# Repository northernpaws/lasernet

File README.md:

# Lasernet

This repository contains the software, hardware, and CAD files for retrofitting lasertag.net Falcon systems with an open-source platform. This involves replacing the PCBs in the tagger and vest units with new Zigbee-controlled PCBs, and having a computer with a Zigbee radio to communicate with them and run the game supervisor software. Additional devices, such as tablets, can be used to manage games over a web interface.

This project is currently a work-in-progress until release v1.0.0. More details for how to assemble the system will be added below as it evolves.

[Tagger Schematics (KiCanvas)](https://kicanvas.org/?github=https%3A%2F%2Fgithub.com%2Fnorthernpaws%2Flasernet%2Fblob%2Fmain%2Ftagger%2Fhardware%2Ftagger.kicad_pro)

## Components

 - An existing lasertag.net Falcon system
 - The retrofit PCBs for the taggers and vests
 - A computer to run the game supervisor
 - A Zigbee interface for the supervisor computer

### Game Supervisor/Controller Computer

For this system you need some type of computer to run the Zigbee interface and game controller software that connects to the units and manages their state, health, etc.

This PC replaces the need for all the units in the system to connect back to an Android tablet over Wifi like the stock laserag.net system does, eliminating Wifi instability from the tablet sleeping, being powered off, battery running out, etc.

We particularly like refurbished Lenovo ThinkCentre Tiny's (such as the M900) for their compact size, power management features (such as auto-power on after power loss), multi-display options, ample USB powers, and an ethernet port, Wifi, and Bluetooth package that gives many options for connectivity. Their reburbished prices are also incredibly afforable, with an M900 with an i7 coming in at around $100CAD, and being office PCs their refurbishment condition tends to be excellent.

### Computer to Zigbee Interface

To communicate with the new units you'll need some type of Zigbee radio or relay that can serve as the Zigbee network coordinator, and allow the PC running the management software to communicate with it. 

Initial software support will be for XBee 3 units in API Mode connected over USB serial, and Texas Instruments Z-Stack devices such as the SMLIGHT SLZB-06M.

We personally like the SMLIGHT SLZB-06M as it can be powered with PoE, simplifying running it to a mount ~12ft up the wall by using a single cable without needing to source additional power at the mounting location. The SLZB-06M is also highly configurable, has suitable range for most indoor arenas, all bundled up into a nice small and portable package that's easy to mount.

## Motivation

I was hired early in 2025 by a center to help repair their lasertag.net Falcon system. The more units I repaired, the more I discovered just how poorly designed the electronics and software components where. The failing units are becoming so regular that I cannot reasonably keep up with them, I'm up to fixing about 5-7 a week with common failures that could have be completely avoided with better mechanical and software design and robust testing that lasertag.net should have done.

I was in regular contact with technical support from the company for several weeks, until they stopped responding after I asked them to connect me to someone I could arrange warrenty repairs with. Likewise, the owner of the business was speaking to their sale representative and a marketing director, who both stopped responding when he asked about repairs and replacement parts. 

The electronics are missing essential safety components, such as a battery charge controller, and some use bad batches of the outdated ESP-12-E (ESP8266 MOD) modules that I've had to replace with the newer ESP-12-F modules on several units to solve Wifi connection problems. The mechanical design around the electronics is also full of issues, such as lacking strain relief on some cables ripping JST connectors off the circuit board under certain common failure conditions.

The software is not robust - missing retry and reconnection mechanisms that cause any minor Wifi instability to result in units dropping out of ongoing games, with no mechanism to reconnect them when they're connected again moments later. The software also relies on all of the game units (possible 20-40+ devices depending on the setup!) having a stable connection to a TCP server running on an Android tablet. If the tablet sleeps, then packets start to be dropped or delayed and causes a myriad of game glitches.

These ongoing issues, and more, have caused the center to loose very large party bookings due to a lack of functional units limiting laser tag game sizes, and have left many players frustrated when a unit fails mid-game and they can't participate.

## Roadmap

Since the business has all of these tagger and vest units that have rebust shells and sewing, we've decided as a "Phase 1" to replace all of the PCBs in the taggers and vests with our own, and then connect them to our own set of software for game management. This will give the business full control over how the system runs, where the failure points are, and allow us to set up a system that's easier for the staff to run and manage.

I'm providing the sources here for anyone else who may be having issues. The goal is that we reach a v2 of this repository where we have the PCB sources files, firmware, and software components required all bundled together into an easily usable package. Eventually I may look at selling replacement retrofit kits and guides.

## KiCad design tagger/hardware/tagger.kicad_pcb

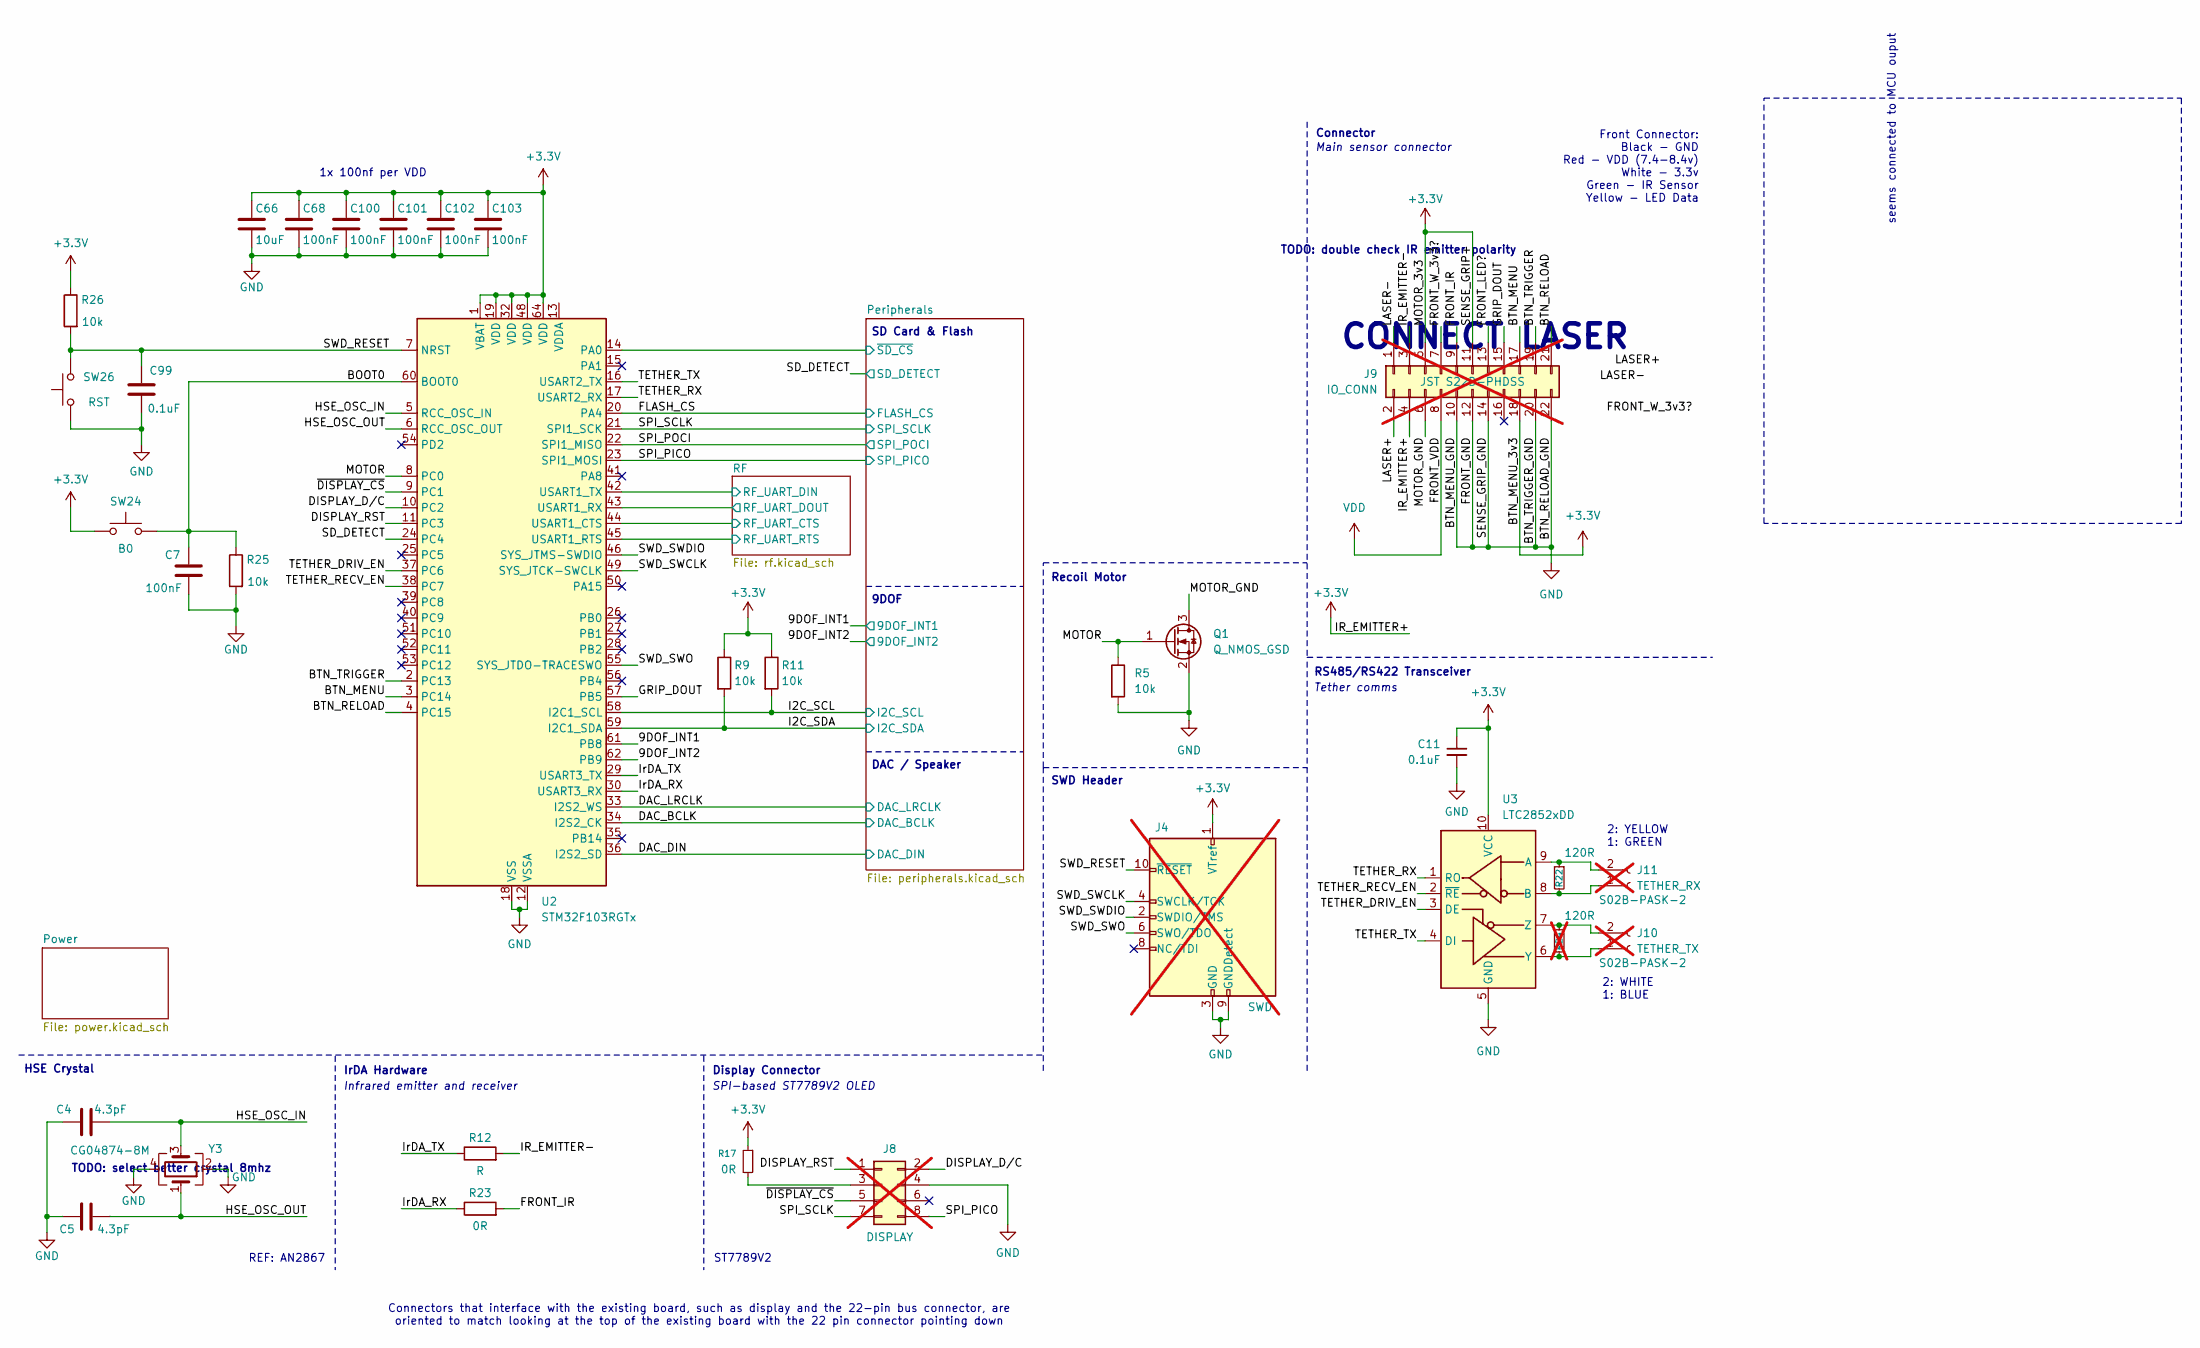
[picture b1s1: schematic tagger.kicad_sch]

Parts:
C4, C5: 4.3pF; C_0402_1005Metric
C7, C68, C100, C101, C102, C103: 100nF; C_0402_1005Metric
C11: 0.1uF
C66: 10uF; C_0402_1005Metric
C99: 0.1uF; C_0402_1005Metric
J4: SWD; PinHeader_2x05_P1.27mm_Vertical; not fitted
J8: DISPLAY; PinHeader_2x04_P2.00mm_Vertical; not fitted
J9: IO_CONN; PinSocket_2x11_P2.00mm_Horizontal; not fitted
J10: TETHER_TX; S02B-PASK-2; not fitted
J11: TETHER_RX; S02B-PASK-2; not fitted
Q1: Q_NMOS_GSD
R5, R9, R11, R25, R26: 10k; R_0402_1005Metric
R12: R; R_0402_1005Metric
R17, R23: 0R; R_0402_1005Metric
R22: 120R; R_0603_1608Metric_Pad0.98x0.95mm_HandSolder
R24: 120R; R_0603_1608Metric_Pad0.98x0.95mm_HandSolder; not fitted
SW24: B0; SW_Push_1P1T_NO_CK_KMR2
SW26: RST; SW_Push_1P1T_NO_CK_KMR2
U2: STM32F103RGTx; LQFP-64_10x10mm_P0.5mm
U3: LTC2852xDD; DFN-10-1EP_3x3mm_P0.5mm_EP1.65x2.38mm
Y3: CG04874-8M; Crystal_SMD_Abracon_ABM3B-4Pin_5.0x3.2mm

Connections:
+3.3V: C11.1, C66.1, C68.1, C100.1, C101.1, C102.1, C103.1, J4.1 (VTref), J9.4, J9.5, J9.11, J9.18, R9.1, R11.1, R17.1, R26.1, SW24.1, U2.1 (VBAT), U2.19 (VDD), U2.32 (VDD), U2.48 (VDD), U2.64 (VDD), U3.10 (VCC); also elsewhere on the board
/9DOF_INT1: U2.61 (PB8); also elsewhere on the board
/9DOF_INT2: U2.62 (PB9); also elsewhere on the board
/BOOT0: C7.1, R25.1, SW24.2, U2.60 (BOOT0)
/BTN_MENU: J9.17, U2.3 (PC14)
/BTN_RELOAD: J9.21, U2.4 (PC15)
/BTN_TRIGGER: J9.19, U2.2 (PC13)
/DAC_BCLK: U2.34 (I2S2_CK); also elsewhere on the board
/DAC_DIN: U2.36 (I2S2_SD); also elsewhere on the board
/DAC_LRCLK: U2.33 (I2S2_WS); also elsewhere on the board
/DISPLAY_D/C: J8.2, U2.10 (PC2)
/DISPLAY_RST: J8.1, U2.11 (PC3)
/FLASH_CS: U2.20 (PA4); also elsewhere on the board
/FRONT_IR: J9.9, R23.2
/FRONT_LED?: J9.13
/FRONT_W_3v3?: J9.7
/GRIP_DOUT: J9.15, U2.57 (PB5)
/HSE_OSC_IN: C4.2, U2.5 (RCC_OSC_IN), Y3.3
/HSE_OSC_OUT: C5.2, U2.6 (RCC_OSC_OUT), Y3.1
/I2C_SCL: R11.2, U2.58 (I2C1_SCL); also elsewhere on the board
/I2C_SDA: R9.2, U2.59 (I2C1_SDA); also elsewhere on the board
/IR_EMITTER-: J9.3, R12.2
/IrDA_RX: R23.1, U2.30 (USART3_RX)
/IrDA_TX: R12.1, U2.29 (USART3_TX)
/LASER+: J9.2
/LASER-: J9.1
/MOTOR: Q1.1 (G), R5.1, U2.8 (PC0)
/MOTOR_GND: J9.6, Q1.3 (D)
/Peripherals/~SD_CS: U2.14 (PA0); also elsewhere on the board
/RF/RF_UART_CTS: U2.44 (USART1_CTS); also elsewhere on the board
/RF/RF_UART_DIN: U2.42 (USART1_TX); also elsewhere on the board
/RF/RF_UART_DOUT: U2.43 (USART1_RX); also elsewhere on the board
/RF/RF_UART_RTS: U2.45 (USART1_RTS); also elsewhere on the board
/SD_DETECT: U2.24 (PC4); also elsewhere on the board
/SPI_PICO: J8.8, U2.23 (SPI1_MOSI); also elsewhere on the board
/SPI_POCI: U2.22 (SPI1_MISO); also elsewhere on the board
/SPI_SCLK: J8.7, U2.21 (SPI1_SCK); also elsewhere on the board
/SWD_RESET: C99.2, J4.10 (~RESET), R26.2, SW26.2, U2.7 (NRST)
/SWD_SWCLK: J4.4 (SWCLK/TCK), U2.49 (SYS_JTCK-SWCLK)
/SWD_SWDIO: J4.2 (SWDIO/TMS), U2.46 (SYS_JTMS-SWDIO)
/SWD_SWO: J4.6 (SWO/TDO), U2.55 (SYS_JTDO-TRACESWO)
/TETHER_DRIV_EN: U2.37 (PC6), U3.3 (DE)
/TETHER_RECV_EN: U2.38 (PC7), U3.2 (~RE)
/TETHER_RX: U2.17 (USART2_RX), U3.1 (RO)
/TETHER_TX: U2.16 (USART2_TX), U3.4 (DI)
/~DISPLAY_CS: J8.5, U2.9 (PC1)
GND: C4.1, C5.1, C7.2, C11.2, C66.2, C68.2, C99.1, C100.2, C101.2, C102.2, C103.2, J4.3 (GND), J4.5 (GND), J4.9 (GNDDetect), J8.4, J9.10, J9.12, J9.14, J9.20, J9.22, Q1.2 (S), R5.2, R25.2, SW26.1, U2.12 (VSSA), U2.18 (VSS), U2.31 (VSS), U2.47 (VSS), U2.63 (VSS), U3.5 (GND), U3.11 (GND), Y3.2, Y3.4; also elsewhere on the board
unnamed: J8.3, R17.2
unnamed: J10.1, R24.2, U3.6 (Y)
unnamed: J10.2, R24.1, U3.7 (Z)
unnamed: J11.1, R22.2, U3.8 (B)
unnamed: J11.2, R22.1, U3.9 (A)
VDD: J9.8; also elsewhere on the board

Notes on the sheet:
CONNECT LASER
SPI-based ST7789V2 OLED
2: YELLOW 1: GREEN
Tether comms
ST7789V2
SWD Header
HSE Crystal
TODO: select better crystal 8mhz
IrDA Hardware
REF: AN2867
DAC / Speaker
RS485/RS422 Transceiver
1x 100nf per VDD
TODO: double check IR emitter polarity
Display Connector
Connector
seems connected to MCU ouput
SD Card & Flash
Recoil Motor
2: WHITE 1: BLUE
Main sensor connector
Connectors that interface with the existing board, such as display and the 22-pin bus connector, are oriented to match looking at the top of the existing board with the 22 pin connector pointing down
Front Connector: Black - GND Red - VDD (7.4-8.4v) White - 3.3v Green - IR Sensor Yellow - LED Data
Infrared emitter and receiver
9DOF

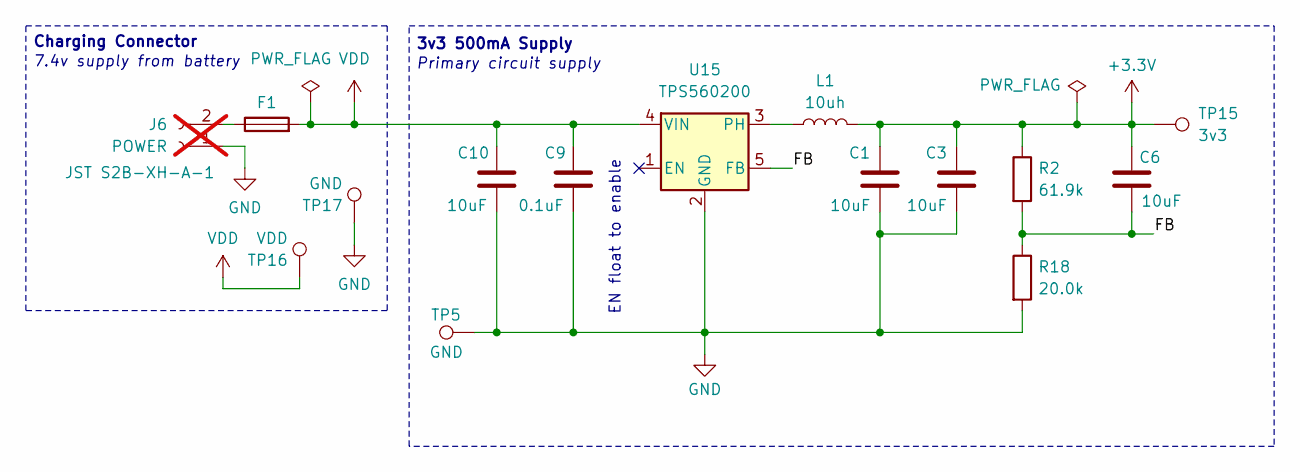
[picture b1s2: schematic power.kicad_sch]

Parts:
C1, C3, C6, C10: 10uF; C_0402_1005Metric
C9: 0.1uF; C_0402_1005Metric
F1: Fuse; Fuse_0805_2012Metric
J6: POWER; JST_XH_S2B-XH-A-1_1x02_P2.50mm_Horizontal; not fitted
L1: 10uh; L_0603_1608Metric
R2: 61.9k; R_0402_1005Metric
R18: 20.0k; R_0402_1005Metric
TP5: GND; TestPoint_Bridge_Pitch2.54mm_Drill1.0mm
TP15: 3v3; TestPoint_Pad_D1.5mm
TP16: VDD; TestPoint_Pad_D1.5mm
TP17: GND; TestPoint_Pad_D1.5mm
U15: TPS560200; SOT-23-5

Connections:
+3.3V: C1.1, C3.1, C6.1, L1.2, R2.1, TP15.1; also elsewhere on the board
/Power/FB: C6.2, R2.2, R18.1, U15.5 (FB)
GND: C1.2, C3.2, C9.2, C10.2, J6.1, R18.2, TP5.1, TP17.1, U15.2 (GND); also elsewhere on the board
unnamed: F1.1, J6.2
unnamed: L1.1, U15.3 (PH)
VDD: C9.1, C10.1, F1.2, TP16.1, U15.4 (VIN); also elsewhere on the board

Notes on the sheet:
Charging Connector
7.4v supply from battery
Primary circuit supply
EN float to enable
3v3 500mA Supply

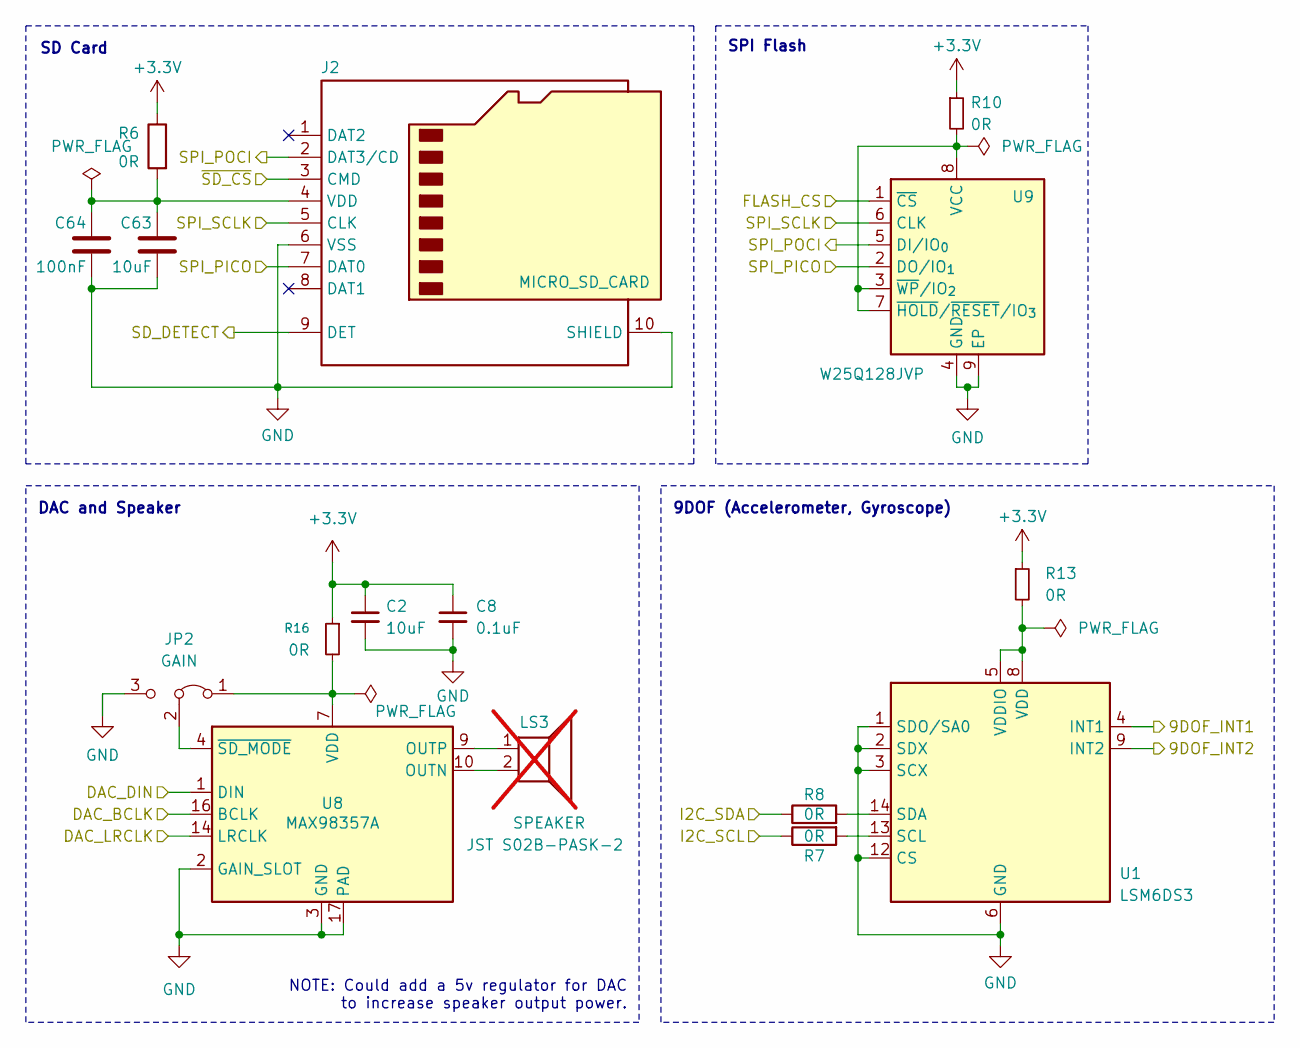
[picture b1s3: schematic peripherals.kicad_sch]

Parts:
C2, C63: 10uF; C_0402_1005Metric
C8: 0.1uF; C_0402_1005Metric
C64: 100nF; C_0402_1005Metric
J2: MICRO_SD_CARD; microSD_HC_Molex_104031-0811
JP2: GAIN; SolderJumper-3_P1.3mm_Bridged12_RoundedPad1.0x1.5mm_NumberL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
LS3: SPEAKER; S02B-PASK-2; not fitted
R6, R7, R8, R10, R13, R16: 0R; R_0402_1005Metric
U1: LSM6DS3; LGA-14_3x2.5mm_P0.5mm_LayoutBorder3x4y
U8: MAX98357A; TQFN-16-1EP_3x3mm_P0.5mm_EP1.23x1.23mm
U9: W25Q128JVP; WSON-8-1EP_6x5mm_P1.27mm_EP3.4x4.3mm

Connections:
+3.3V: C2.1, C8.1, R6.1, R10.1, R13.1, R16.1; also elsewhere on the board
/9DOF_INT1: U1.4 (INT1); also elsewhere on the board
/9DOF_INT2: U1.9 (INT2); also elsewhere on the board
/DAC_BCLK: U8.16 (BCLK); also elsewhere on the board
/DAC_DIN: U8.1 (DIN); also elsewhere on the board
/DAC_LRCLK: U8.14 (LRCLK); also elsewhere on the board
/FLASH_CS: U9.1 (~CS); also elsewhere on the board
/I2C_SCL: R7.1; also elsewhere on the board
/I2C_SDA: R8.1; also elsewhere on the board
/Peripherals/~SD_CS: J2.3 (CMD); also elsewhere on the board
/SD_DETECT: J2.9 (DET); also elsewhere on the board
/SPI_PICO: J2.7 (DAT0), U9.2 (DO/IO_{1}); also elsewhere on the board
/SPI_POCI: J2.2 (DAT3/CD), U9.5 (DI/IO_{0}); also elsewhere on the board
/SPI_SCLK: J2.5 (CLK), U9.6 (CLK); also elsewhere on the board
GND: C2.2, C8.2, C63.2, C64.2, J2.6 (VSS), J2.10 (SHIELD), JP2.3 (B), U1.1 (SDO/SA0), U1.2 (SDX), U1.3 (SCX), U1.6 (GND), U1.7 (GND), U1.12 (CS), U8.2 (GAIN_SLOT), U8.3 (GND), U8.11 (GND), U8.15 (GND), U8.17 (PAD), U9.4 (GND), U9.9 (EP); also elsewhere on the board
unnamed: C63.1, C64.1, J2.4 (VDD), R6.2
unnamed: JP2.1 (A), R16.2, U8.7 (VDD), U8.8 (VDD)
unnamed: JP2.2 (C), U8.4 (~SD_MODE)
unnamed: R7.2, U1.13 (SCL)
unnamed: R8.2, U1.14 (SDA)
unnamed: R13.2, U1.5 (VDDIO), U1.8 (VDD)
unnamed: LS3.2, U8.10 (OUTN)
unnamed: LS3.1, U8.9 (OUTP)
unnamed: R10.2, U9.3 (~WP/IO_{2}), U9.7 (~HOLD/~RESET/IO_{3}), U9.8 (VCC)

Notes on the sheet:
DAC and Speaker
SPI Flash
NOTE: Could add a 5v regulator for DAC to increase speaker output power.
9DOF (Accelerometer, Gyroscope)
SD Card

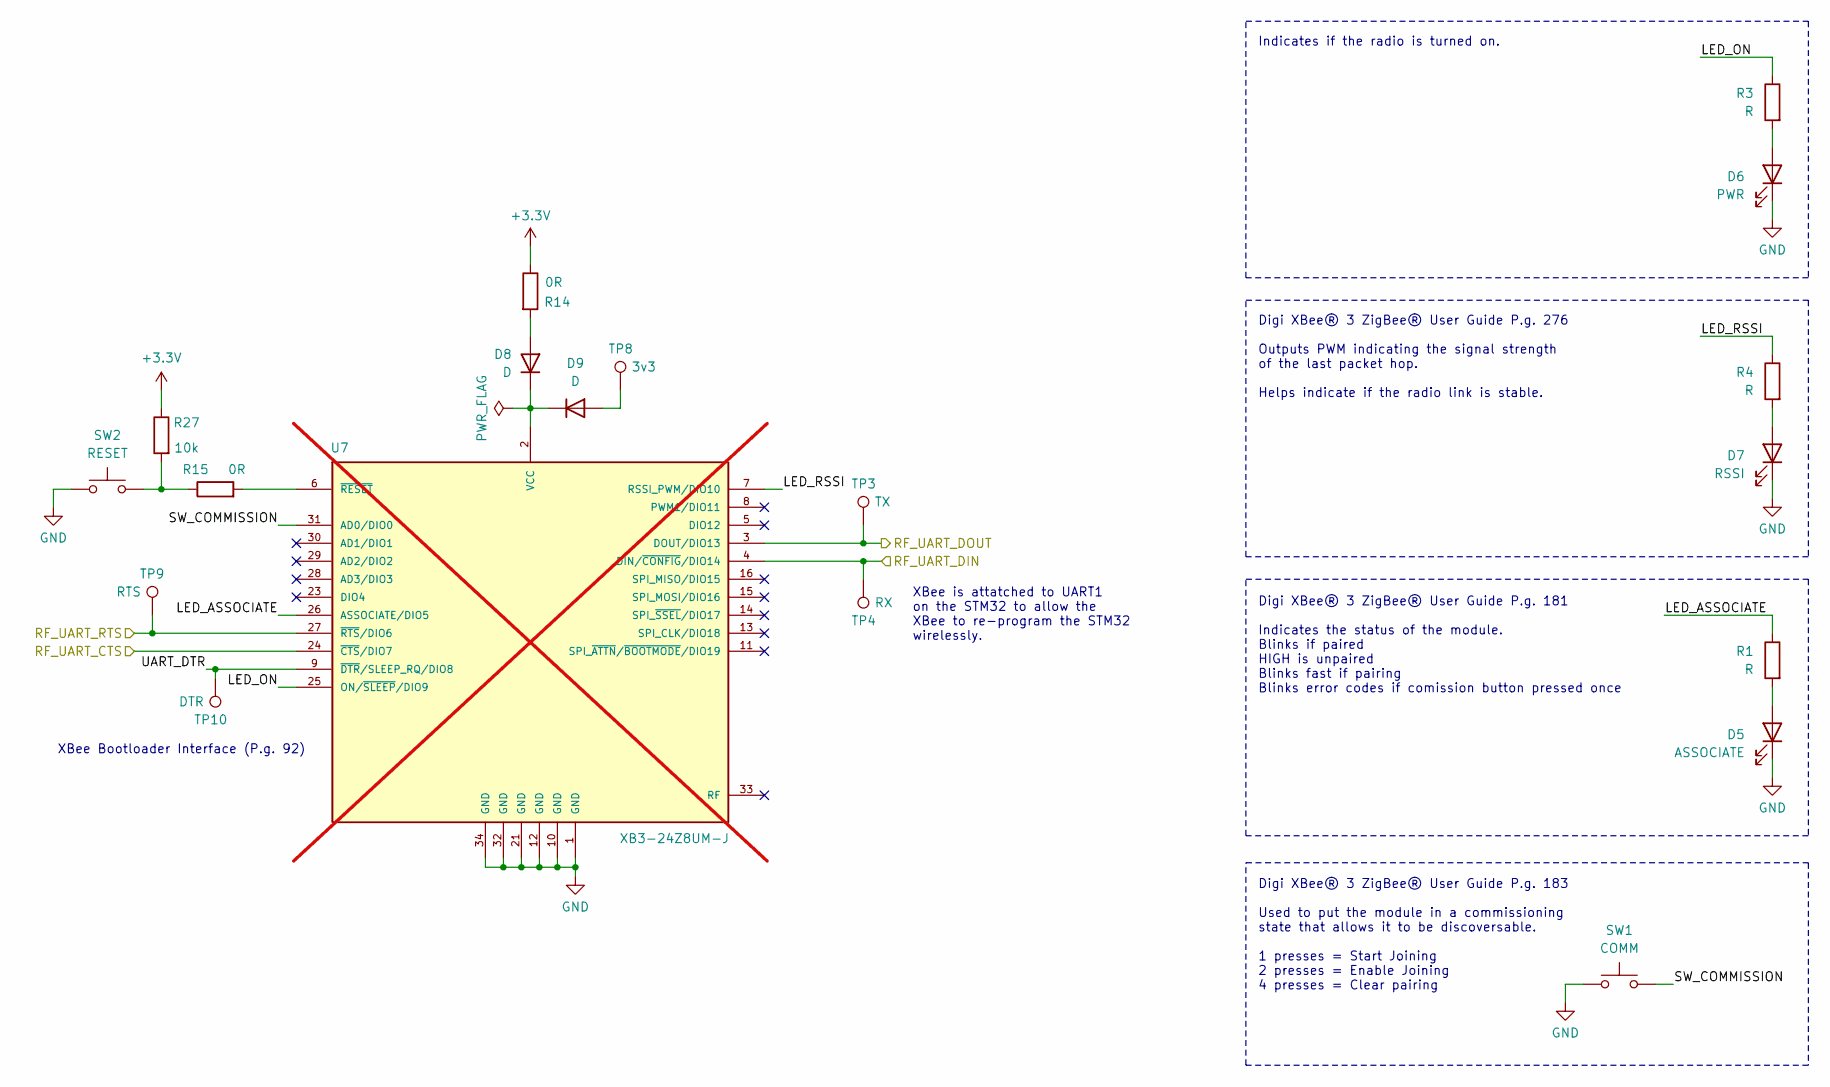
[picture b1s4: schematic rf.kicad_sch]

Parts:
D5: ASSOCIATE; LED_0603_1608Metric
D6: PWR; LED_0603_1608Metric
D7: RSSI; LED_0603_1608Metric
D8, D9: D; D_0402_1005Metric
R1, R3, R4: R; R_0402_1005Metric
R14, R15: 0R; R_0402_1005Metric
R27: 10k; R_0402_1005Metric
SW1: COMM; SW_Push_1P1T_NO_CK_KMR2
SW2: RESET; SW_Push_1P1T_NO_CK_KMR2
TP3: TX; TestPoint_Bridge_Pitch2.54mm_Drill1.0mm
TP4: RX; TestPoint_Bridge_Pitch2.54mm_Drill1.0mm
TP8: 3v3; TestPoint_Pad_D1.0mm
TP9: RTS; TestPoint_Pad_D1.0mm
TP10: DTR; TestPoint_Pad_D1.0mm
U7: XB3-24Z8UM-J; XCVR_XB3-24Z8UM-J; not fitted

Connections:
+3.3V: R14.1, R27.1; also elsewhere on the board
/RF/LED_ASSOCIATE: R1.1, U7.26 (ASSOCIATE/DIO5)
/RF/LED_ON: R3.1, U7.25 (ON/~SLEEP/DIO9)
/RF/LED_RSSI: R4.1, U7.7 (RSSI_PWM/DIO10)
/RF/RF_UART_CTS: U7.24 (~CTS/DIO7); also elsewhere on the board
/RF/RF_UART_DIN: TP4.1, U7.4 (DIN/~CONFIG/DIO14); also elsewhere on the board
/RF/RF_UART_DOUT: TP3.1, U7.3 (DOUT/DIO13); also elsewhere on the board
/RF/RF_UART_RTS: TP9.1, U7.27 (~RTS/DIO6); also elsewhere on the board
/RF/SW_COMMISSION: SW1.2, U7.31 (AD0/DIO0)
/RF/UART_DTR: TP10.1, U7.9 (~DTR/SLEEP_RQ/DIO8)
GND: D5.1 (K), D6.1 (K), D7.1 (K), SW1.1, SW2.1, U7.1 (GND), U7.10 (GND), U7.12 (GND), U7.21 (GND), U7.32 (GND), U7.34 (GND); also elsewhere on the board
unnamed: D5.2 (A), R1.2
unnamed: D6.2 (A), R3.2
unnamed: D7.2 (A), R4.2
unnamed: D8.2 (A), R14.2
unnamed: D8.1 (K), D9.1 (K), U7.2 (VCC)
unnamed: D9.2 (A), TP8.1
unnamed: R15.1, R27.2, SW2.2
unnamed: R15.2, U7.6 (~RESET)

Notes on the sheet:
Indicates if the radio is turned on.
Digi XBee® 3 ZigBee® User Guide P.g. 183 Used to put the module in a commissioning state that allows it to be discoversable. 1 presses = Start Joining 2 presses = Enable Joining 4 presses = Clear pairing
XBee Bootloader Interface (P.g. 92)
Digi XBee® 3 ZigBee® User Guide P.g. 276 Outputs PWM indicating the signal strength of the last packet hop. Helps indicate if the radio link is stable.
XBee is attatched to UART1 on the STM32 to allow the XBee to re-program the STM32 wirelessly.
Digi XBee® 3 ZigBee® User Guide P.g. 181 Indicates the status of the module. Blinks if paired HIGH is unpaired Blinks fast if pairing Blinks error codes if comission button pressed once

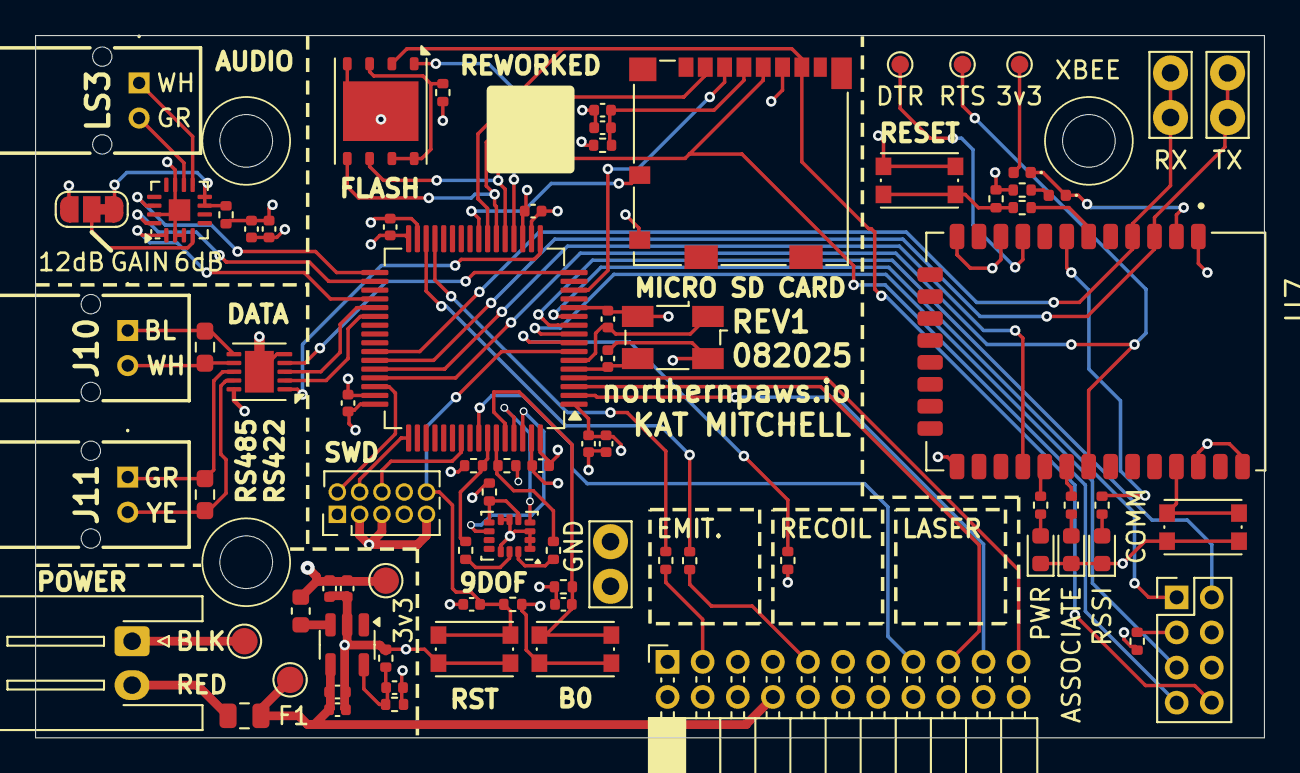
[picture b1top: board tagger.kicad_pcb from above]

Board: 4 copper layers, 70.0 x 40.0 mm, 80 parts (0 on the bottom side), 73 nets.

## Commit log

2025-07-15 feat(distro): initial menuconfig setup
2025-07-15 feat(distro): enable rauc update images in platformconfig
2025-07-15 fix(distro): add missing barebox MD5
2025-07-15 chore: add python3.11-venv to instructions
2025-07-15 fix(distro): add correct barebox version and md5 hash
2025-07-15 feat(distro): add barebox config file with `ptxdist menuconfig barebox`
2025-07-15 feat(distro): initial configure and build
2025-07-15 feat(distro): updated kernel configs
2025-07-15 fix(distro): removed acidentally comitted image
2025-07-15 feat(distro): enable building partitioned hd image
2025-07-15 chore: reorganize distro into controller folder
2025-07-15 chore(controller/distro): delete unused platform configs
2025-07-15 feat(controller/software): init cargo crate
2025-07-15 ci: add workflow for controller software and distro
2025-07-15 ci: fix formatting of script blocks
2025-07-15 ci: fix formatting of run line
2025-07-15 ci: use apt-add-repository action
2025-07-15 ci: use caching action for apt packages
2025-07-15 ci: revert pengutronix signing key change
2025-07-15 ci: fix syntax for adding apt repository
2025-07-15 ci: add missing apt packages for distro compilation
2025-07-15 ci: add python 3.11 setup
2025-07-15 ci: fix dependency install for ptxdist
2025-07-15 ci: add missing libxml-parser-perl dependency
2025-07-15 feat: add README.md
2025-07-15 ci(controller): add path scoping to workflow triggers
2025-07-15 ci: fix cache and artifact paths
2025-07-15 ci: add workflow to watch paths
2025-07-19 feat(controller/distro): fix missing EFI partition
2025-07-19 fix(controller/distro): barebox bootloader not starting on x86
2025-07-20 feat(controller/distro): update barebox settings and start adding environment config
2025-07-20 chore: add components to README.md
2025-07-20 ci: cache build files even on failure
2025-07-20 feat(controller/distro): enable USB keyboard support in bootloader
2025-07-20 feat(controller): add color-eyre to crate
2025-07-20 feat: add KiCad project for tagger
2025-07-20 feat: add firmware for tagger
2025-07-20 chore: add KiCanvas link to README.md
2025-07-20 ci: add CI workflow for tagger tests
2025-07-20 feat(tagger/firmware): select valid pins for SPI bus and display
2025-07-20 ci: fix working directory for tagger
2025-07-20 feat(tagger/firmware): add remaining display setup code
2025-07-20 ci(tagger): fix typo in `cargo test --verboses`
2025-07-20 fix(tagger/firmware): disable building tests by default
2025-07-20 ci(tagger): add rust build caching
2025-07-20 fix(controller/distro): no input in bootloader shell due to lacking EFI serial driver
2025-07-20 feat(controller/distro): add nv barebox env variables
2025-07-20 feat(controller/distro): enable virtual console and framebuffer support
2025-07-21 fix(controller/distro): incorrect partition UUID causing repart to miss existing partitions
2025-07-21 feat(controller/distro): fix disks not registering in kernel
2025-07-21 feat(controller/distro): configure bootchooser for logical partition numbering
2025-07-21 fix(controller/software): missing return type
2025-07-21 feat(controller/distro): add wayland support for kiosk video
2025-07-21 feat(controller/distro): start adding video rendering support
2025-07-21 feat(controller/distro): disable loading environment files in bootloader
2025-07-21 fix(controller/distro): bootloader attempting to use console colors on VGA
2025-07-21 Revert "feat(controller/distro): start adding video rendering support"
    This reverts commit be612bbbdf42c39eecb046a7faa19d68333d552c.
2025-07-21 Revert "feat(controller/distro): add wayland support for kiosk video"
    This reverts commit d9a9eb7e3332762ccb365ba2e9b88f690e8b7535.
2025-07-21 feat(controller/distro): add missing DTSI for barebox-state
2025-07-22 feat(distro): add barebox state DTS and derrived image
2025-07-22 fix(distro): bootloader selecting wrong partition and kernel missing serial console
2025-07-22 feat(controller/software): start adding scoreboard window
2025-07-22 feat(distro): enable USB drivers and mass storage
2025-07-22 feat(distro): enable mesa and weston
2025-07-23 feat(distro): add missing python3-yaml dependency
2025-07-23 chore(tagger): schematic reorganization
2025-07-23 feat(controller): start working on splash screen
2025-07-23 feat(distro): enable mesa, wayland and weston-shell
2025-07-23 fix(distro): root A/B partitions too small for root image with Wayland
2025-07-23 chore(distro): update instructions in README.md
2025-07-23 ci(controller): temporarily remove cargo tests while working on distro
2025-07-23 ci(controller): add missing python3-yaml dependency
2025-07-23 ci(controller): fix permission errors on restoring ptxdist cache
2025-07-23 ci(controller): change python dependency to pip install
2025-07-23 ci(controller): remove broken pip cache directive
2025-07-23 ci(controller): pin ubuntu release
2025-07-23 fix(distro): update platformconfig to use absolute path to barebox.config
2025-07-23 ci(controller): ensure that ptxdist configs don't crash the build
2025-07-23 chore(controller/distro): update README.md
2025-07-27 feat(tagger): add notes to schematic
2025-07-27 chore(tagger): add hardware .gitignore
2025-07-27 chore(tagger): clean up kicad files
2025-07-27 chore: remove acidental git modules folder
2025-07-31 feat: schematic organization
2025-07-31 feat: start board layout
2025-07-31 feat: board routing and RS485 implementation
2025-07-31 feat: more board layout
2025-08-05 feat: various board routing changes
2025-08-14 chore: PCB routing and layout
2025-08-14 feat: add IR routing, fix component sizes
2025-08-14 feat: added missing 3d models
2025-08-14 feat: audio routing and test points
2025-08-25 feat: more pcb layout
2025-08-26 feat: replace tether comms with full-duplex
2025-08-26 feat: schematic organization, added SD card connections
2025-08-27 feat: replace RS485 transceiver, fix DRC warnings
